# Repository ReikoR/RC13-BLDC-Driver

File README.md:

RC13-BLDC-Driver
================

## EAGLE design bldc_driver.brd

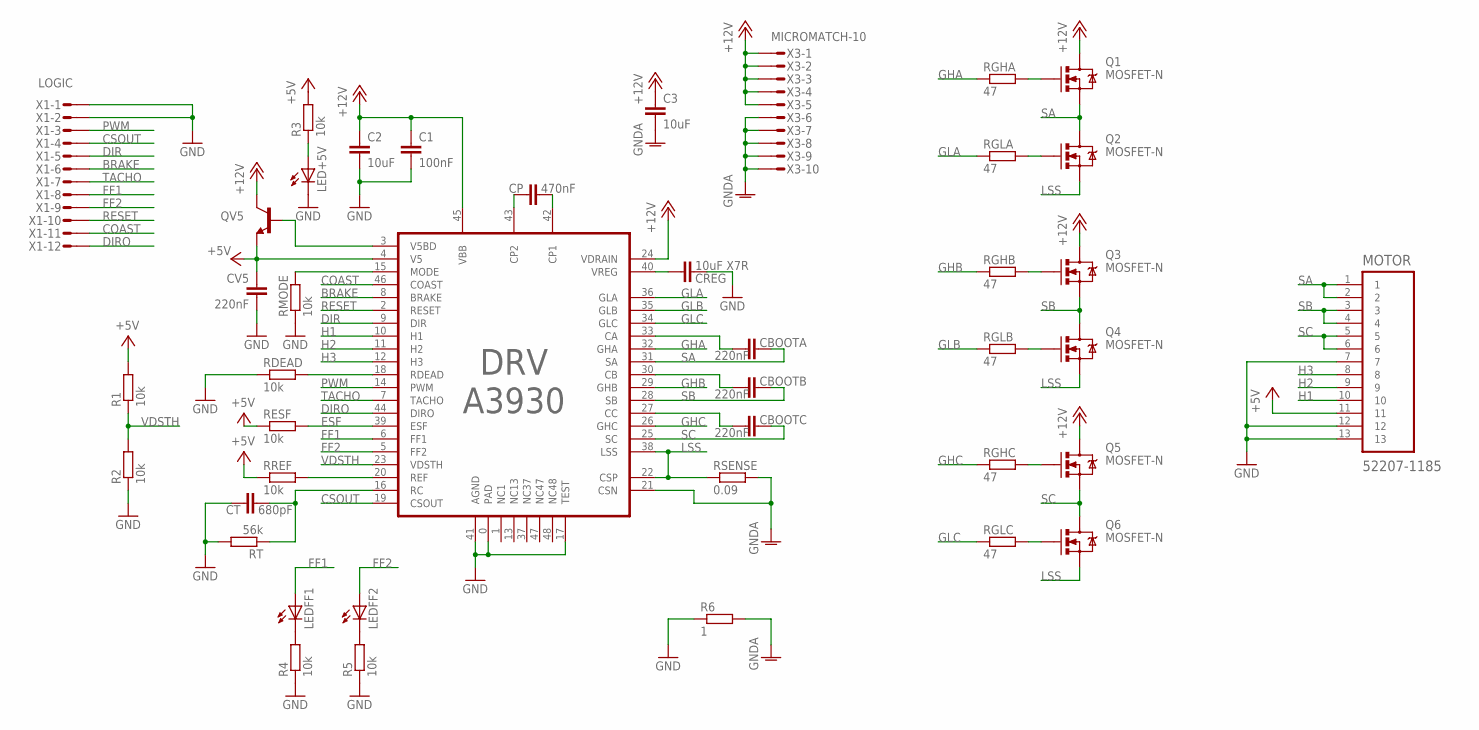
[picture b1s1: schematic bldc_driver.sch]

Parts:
C1: 100nF; C0603
C2, C3: 10uF; C1206K
CBOOTA: 220nF; C0603
CBOOTB: 220nF; C0603
CBOOTC: 220nF; C0603
CP: 470nF; C0603
CREG: 10uF X7R; C1206K
CT: 680pF; C0603
CV5: 220nF; C0603
DRV: A3930; LQFP-48
LED+5V: LEDCHIPLED_0603; CHIPLED_0603
LEDFF1, LEDFF2: LEDCHIPLED_0603; CHIPLED_0603
MOTOR: 52207-1185; MOLEX_52207-1185
Q1, Q2, Q3, Q4, Q5, Q6: MOSFET-N; SO08
QV5: TRANSISTOR_NPNSOT23; SOT23
R1, R2, R3, R4, R5: 10k; R0603
R6: 1; R0603
RDEAD: 10k; R0603
RESF: 10k; R0603
RGHA: 47; R0603
RGHB: 47; R0603
RGHC: 47; R0603
RGLA: 47; R0603
RGLB: 47; R0603
RGLC: 47; R0603
RMODE: 10k; R0603
RREF: 10k; R0603
RSENSE: 0.09; R2010
RT: 56k; R0603
X1: LOGIC; MICROMATCH-12
X3: MICROMATCH-10

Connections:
+5V: CV5.2, DRV.4 (V5), MOTOR.11, QV5.2 (E), R1.2, R3.2, RESF.1, RREF.1
+12V: C1.1, C2.1, C3.1, DRV.24 (VDRAIN), DRV.45 (VBB), Q1.5 (D), Q1.6 (D), Q1.7 (D), Q1.8 (D), Q3.5 (D), Q3.6 (D), Q3.7 (D), Q3.8 (D), Q5.5 (D), Q5.6 (D), Q5.7 (D), Q5.8 (D), QV5.3 (C), X3.1, X3.2, X3.3, X3.4, X3.5
BRAKE: DRV.8 (BRAKE), X1.6
COAST: DRV.46 (COAST), X1.11
CSOUT: DRV.19 (CSOUT), X1.4
DIR: DRV.9 (DIR), X1.5
DIRO: DRV.44 (DIRO), X1.12
ESF: DRV.39 (ESF), RESF.2
FF1: DRV.6 (FF1), LEDFF1.A, X1.8
FF2: DRV.5 (FF2), LEDFF2.A, X1.9
GHA: DRV.32 (GHA), RGHA.1
GHB: DRV.29 (GHB), RGHB.1
GHC: DRV.26 (GHC), RGHC.1
GLA: DRV.36 (GLA), RGLA.1
GLB: DRV.35 (GLB), RGLB.1
GLC: DRV.34 (GLC), RGLC.1
GND: C1.2, C2.2, CREG.2, CT.2, CV5.1, DRV.0 (PAD), DRV.17 (TEST), DRV.41 (AGND), LED+5V.C, MOTOR.7, MOTOR.12, MOTOR.13, R2.1, R4.1, R5.1, R6.1, RDEAD.1, RMODE.1, RT.2, X1.1, X1.2
GNDA: C3.2, DRV.21 (CSN), R6.2, RSENSE.2, X3.6, X3.7, X3.8, X3.9, X3.10
H1: DRV.10 (H1), MOTOR.10
H2: DRV.11 (H2), MOTOR.9
H3: DRV.12 (H3), MOTOR.8
LSS: DRV.22 (CSP), DRV.38 (LSS), Q2.1 (S), Q2.2 (S), Q2.3 (S), Q4.1 (S), Q4.2 (S), Q4.3 (S), Q6.1 (S), Q6.2 (S), Q6.3 (S), RSENSE.1
unnamed: Q1.4 (G), RGHA.2
unnamed: Q2.4 (G), RGLA.2
unnamed: Q3.4 (G), RGHB.2
unnamed: Q4.4 (G), RGLB.2
unnamed: Q5.4 (G), RGHC.2
unnamed: Q6.4 (G), RGLC.2
unnamed: CBOOTA.1, DRV.33 (CA)
unnamed: CREG.1, DRV.40 (VREG)
unnamed: CT.1, DRV.16 (RC), RT.1
unnamed: CP.1, DRV.42 (CP1)
unnamed: CP.2, DRV.43 (CP2)
unnamed: CBOOTB.1, DRV.30 (CB)
unnamed: DRV.18 (RDEAD), RDEAD.2
unnamed: CBOOTC.1, DRV.27 (CC)
unnamed: LED+5V.A, R3.1
unnamed: DRV.20 (REF), RREF.2
unnamed: DRV.15 (MODE), RMODE.2
unnamed: LEDFF1.C, R4.2
unnamed: LEDFF2.C, R5.2
unnamed: DRV.3 (V5BD), QV5.1 (B)
PWM: DRV.14 (PWM), X1.3
RESET: DRV.2 (RESET), X1.10
SA: CBOOTA.2, DRV.31 (SA), MOTOR.1, MOTOR.2, Q1.1 (S), Q1.2 (S), Q1.3 (S), Q2.5 (D), Q2.6 (D), Q2.7 (D), Q2.8 (D)
SB: CBOOTB.2, DRV.28 (SB), MOTOR.3, MOTOR.4, Q3.1 (S), Q3.2 (S), Q3.3 (S), Q4.5 (D), Q4.6 (D), Q4.7 (D), Q4.8 (D)
SC: CBOOTC.2, DRV.25 (SC), MOTOR.5, MOTOR.6, Q5.1 (S), Q5.2 (S), Q5.3 (S), Q6.5 (D), Q6.6 (D), Q6.7 (D), Q6.8 (D)
TACHO: DRV.7 (TACHO), X1.7
VDSTH: DRV.23 (VDSTH), R1.1, R2.2

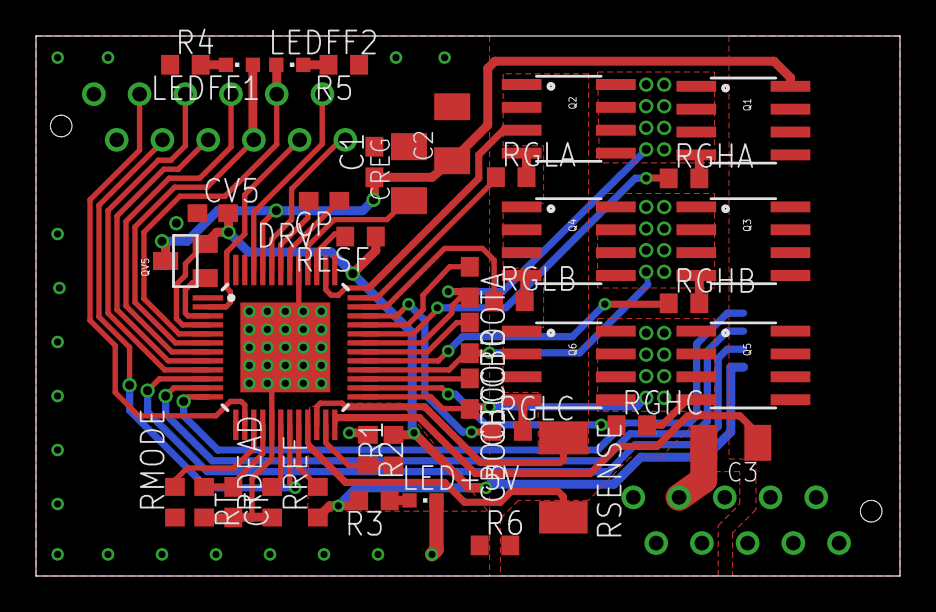
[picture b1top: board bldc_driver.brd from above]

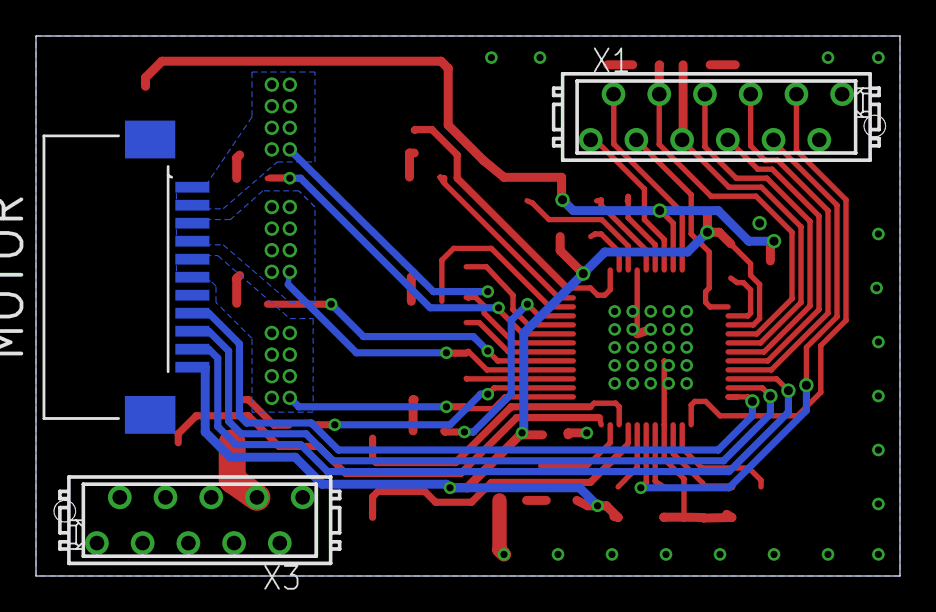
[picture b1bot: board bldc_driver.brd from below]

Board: 2 copper layers, 48.0 x 30.0 mm, 42 parts (3 on the bottom side), 49 nets.

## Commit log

2013-06-16 Added version 0.1 Eagle files
2013-08-19 Changed hall sensor connections to proper order

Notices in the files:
parts and their libraries:
SparkFun-DiscreteSemi: Licensing: CC v3.0 Share-Alike You are welcome to use this library for commercial purposes.
